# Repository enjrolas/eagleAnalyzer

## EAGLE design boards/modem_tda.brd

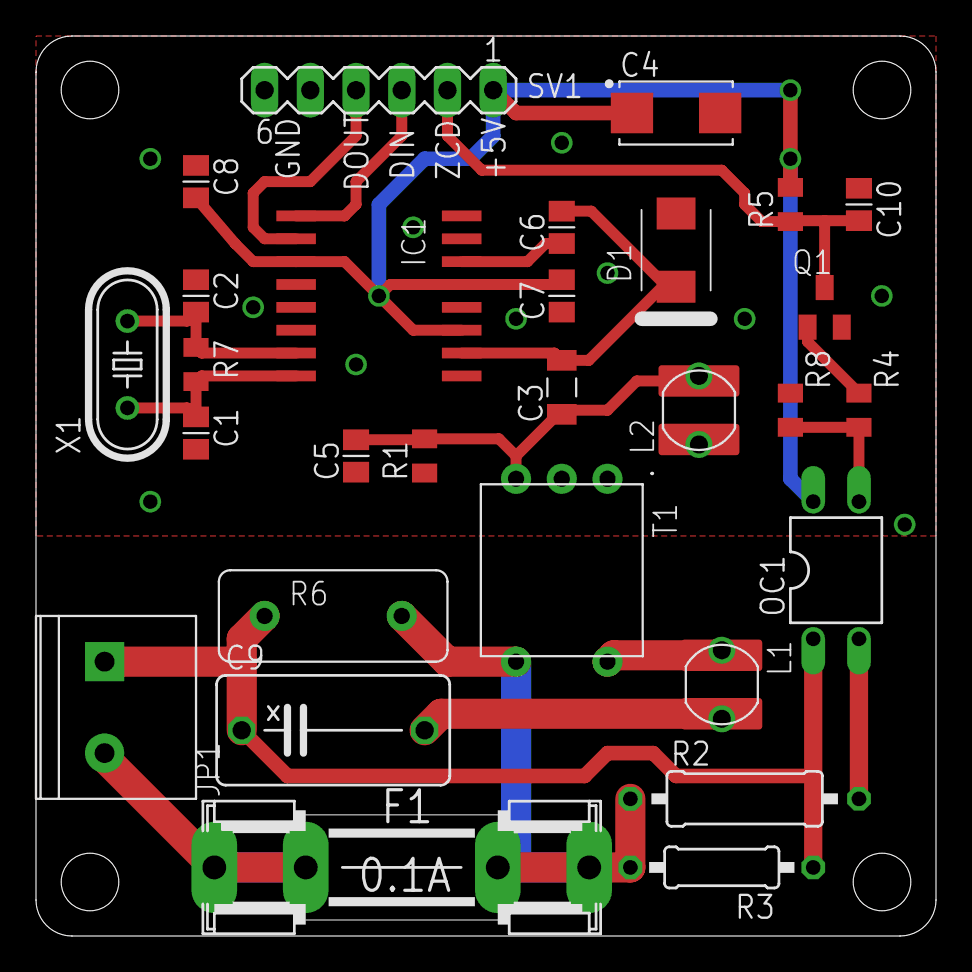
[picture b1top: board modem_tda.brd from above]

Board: 2 copper layers, 50.0 x 50.0 mm, 29 parts (0 on the bottom side), 18 nets.

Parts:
C1, C2: 27pF; CAPC2012X145AN
C3: 10 uF 16V; CAPC3215X168N
C4: 100 uF; CAPMP6032X150N
C5, C6, C7, C8: 0.1uF; CAPC2012X145AN
C9: 47nF; XC10B6
C10: 2.2nF; CAPC2012X145AN
D1: SMBJ7.0A; SMBJ
F1: 0.1A; SHK20L
IC1: TDA5051; SO16W
JP1: BLUE_TERM
L1: 47 uH; CD43
L2: 22 uH; CD43
OC1: PC814; DIL04
Q1: 2N3904SOT23; SOT23-BEC
R1: 100; RESC2012X70N
R2: 220K; 0309/12
R3: 1M; 0207/10
R4: 1K; RESC2012X70N
R5: 10K; RESC2012X70N
R6: 10D391K; MOV-10D
R7: 2.2M; RESC2012X70N
R8: 4.7K; RESC2012X70N
SV1: MA06-1
T1: MU-78250; 6-PIN-DIL
X1: 8MHz; HC49/S

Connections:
+5V: C4.+, C7.2, C8.2, IC1.3, IC1.11, IC1.13, OC1.4, R5.2, SV1.1
GND: C1.2, C2.2, C4.-, C5.1, C7.1, C8.1, C10.1, D1.A, IC1.5, IC1.9, IC1.12, L2.1, Q1.E, R1.1, R8.1, SV1.5, SV1.6, T1.1
unnamed: F1.1A, F1.1B, JP1.2
unnamed: F1.2A, F1.2B, R2.1, R3.2, R6.2, T1.4
unnamed: C9.1, JP1.1, OC1.1, R3.1, R6.1
unnamed: OC1.2, R2.2
unnamed: C9.2, L1.2
unnamed: L1.1, T1.6
unnamed: OC1.3, R4.1, R8.2
unnamed: C3.1, C5.2, L2.2, R1.2, T1.3
unnamed: C3.2, C6.2, D1.C, IC1.10
unnamed: C10.2, Q1.C, R5.1, SV1.2
unnamed: C6.1, IC1.14
unnamed: C2.1, IC1.7, R7.2, X1.2
unnamed: C1.1, IC1.8, R7.1, X1.1
unnamed: IC1.1, SV1.3
unnamed: IC1.2, SV1.4
unnamed: Q1.B, R4.2

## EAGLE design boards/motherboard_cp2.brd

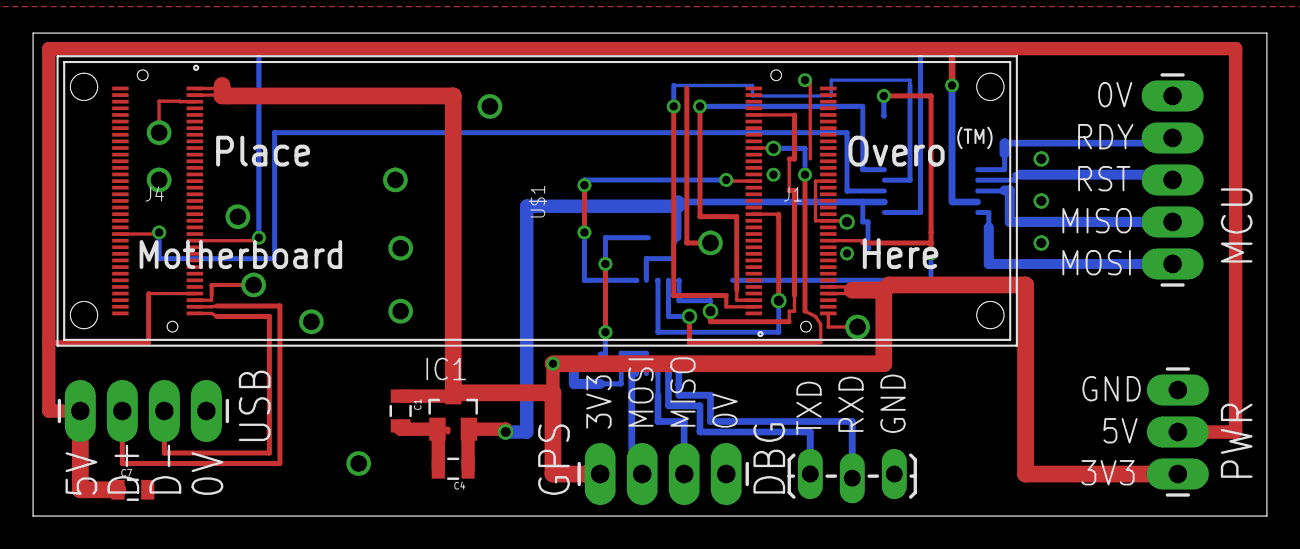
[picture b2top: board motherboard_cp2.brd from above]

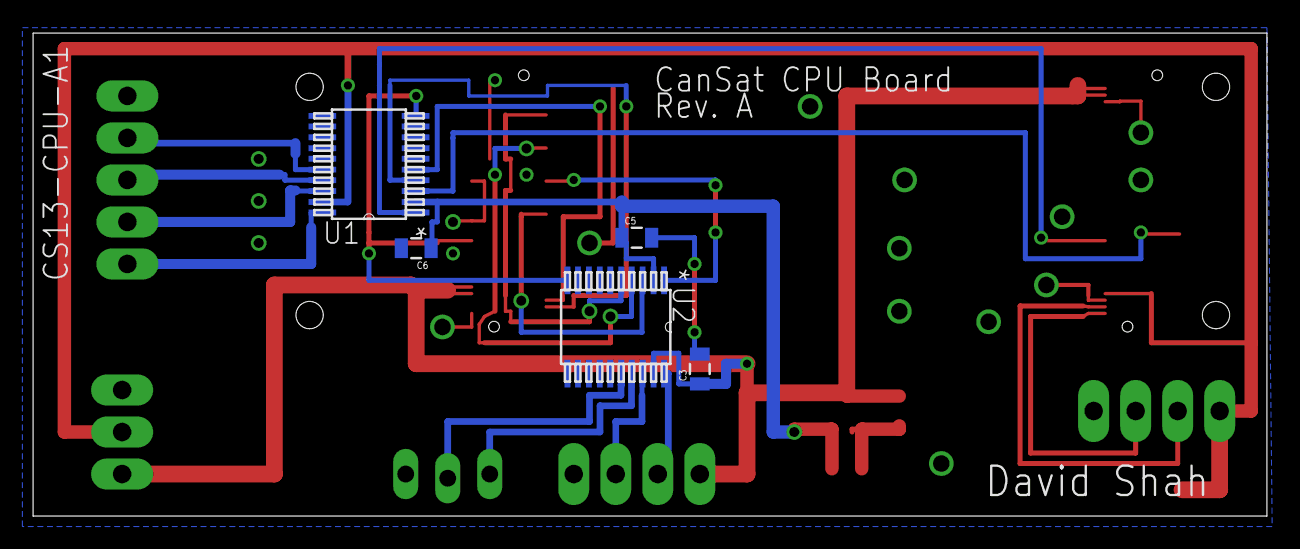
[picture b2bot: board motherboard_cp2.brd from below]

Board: 2 copper layers, 74.6 x 29.2 mm, 15 parts (5 on the bottom side), 23 nets.

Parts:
C1, C3, C4, C5, C6, C7: 1uF; 0805
DEBUG: 1X03_LOCK_LONGPADS
GPS: 1X04_LONGPADS
IC1: MCP1703CB; SOT23
MCU: 1X05_LONGPADS
PWR: 1X03_LONGPADS
U1, U2: TXS0108E_PW_20; PW20
U$1: OVERO
USB: 1X04_LONGPADS

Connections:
1.8V: C4.1, C5.1, C6.1, IC1.2, U1.2, U2.2
3.3V: C1.1, C3.1, GPS.1, IC1.3, PWR.1, U2.19, U$1.J1_66, U$1.J1_67, U$1.J4_1, U$1.J4_2
5V: C7.1, PWR.2, U1.19, U$1.J4_32, USB.1
DBG_RXD: DEBUG.2, U2.16
DBG_TXD: DEBUG.1, U2.17
GND: C1.2, C3.2, C4.2, C5.2, C6.2, C7.2, DEBUG.3, GPS.4, IC1.1, MCU.5, PWR.3, U1.11, U1.12, U1.13, U1.14, U1.15, U2.11, U2.12, U2.13, U2.14, U2.15, U$1.J1_50, U$1.J1_56, U$1.J1_70, U$1.J4_3, U$1.J4_33, USB.4
GPS_RXD: GPS.3, U2.18
GPS_TXD: GPS.2, U2.20
MCU_RDY: MCU.4, U1.16
MCU_RST: MCU.3, U1.17
MCU_RXD: MCU.2, U1.18
MCU_TXD: MCU.1, U1.20
RDY: U1.5, U$1.J1_3
SYSEN: U1.10, U2.10, U$1.J1_59
UART1_RTS: U1.4, U$1.J1_2
UART1_RXD: U1.3, U$1.J4_48
UART1_TXD: U1.1, U$1.J4_24
UART2_RXD: U2.3, U$1.J1_16
UART2_TXD: U2.1, U$1.J1_21
UART3_RXD: U2.5, U$1.J1_31
UART3_TXD: U2.4, U$1.J1_26
USB_DM: U$1.J4_35, USB.3
USB_DP: U$1.J4_34, USB.2

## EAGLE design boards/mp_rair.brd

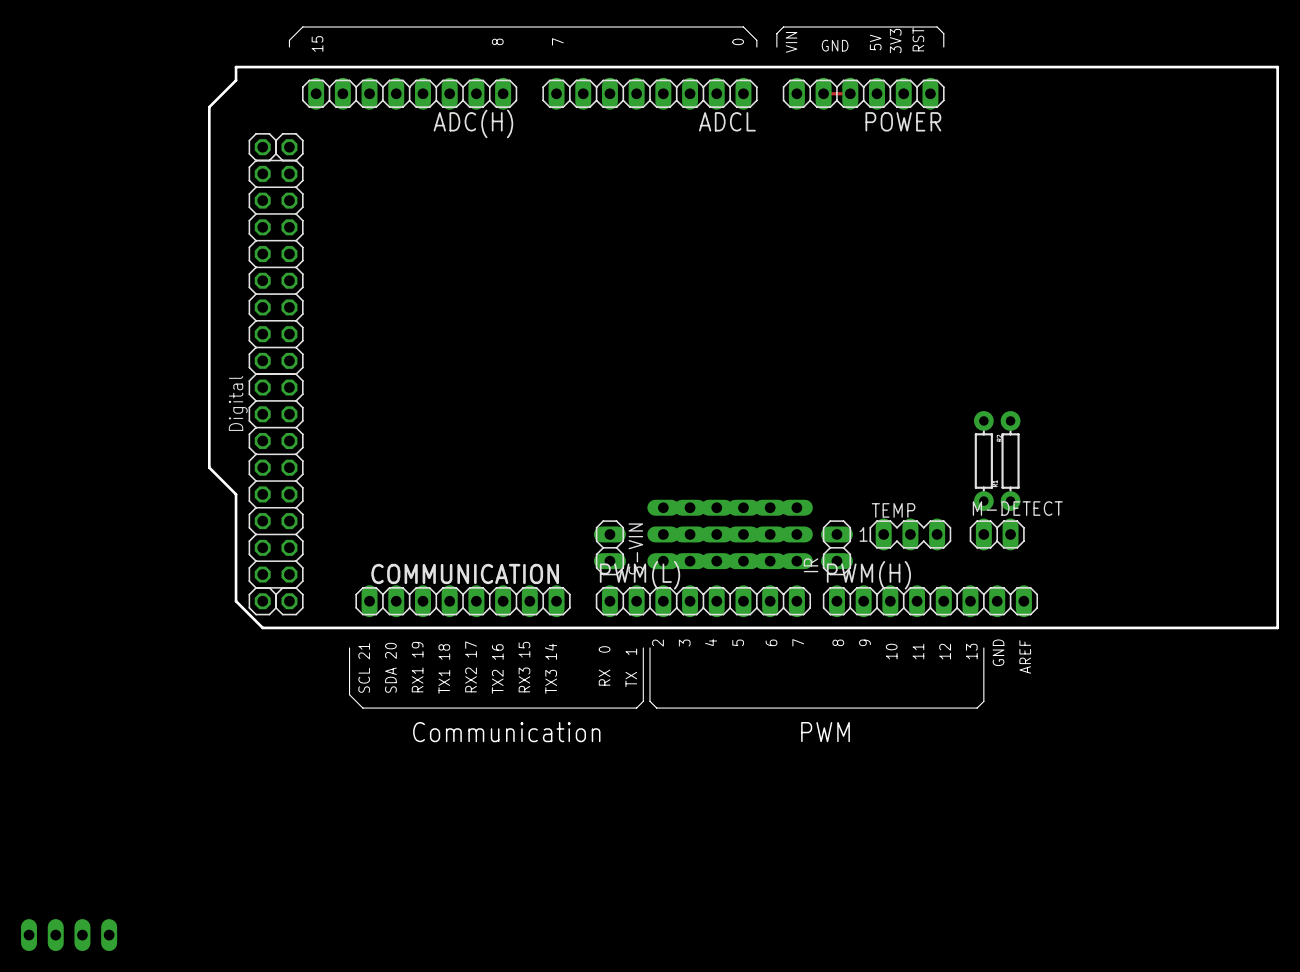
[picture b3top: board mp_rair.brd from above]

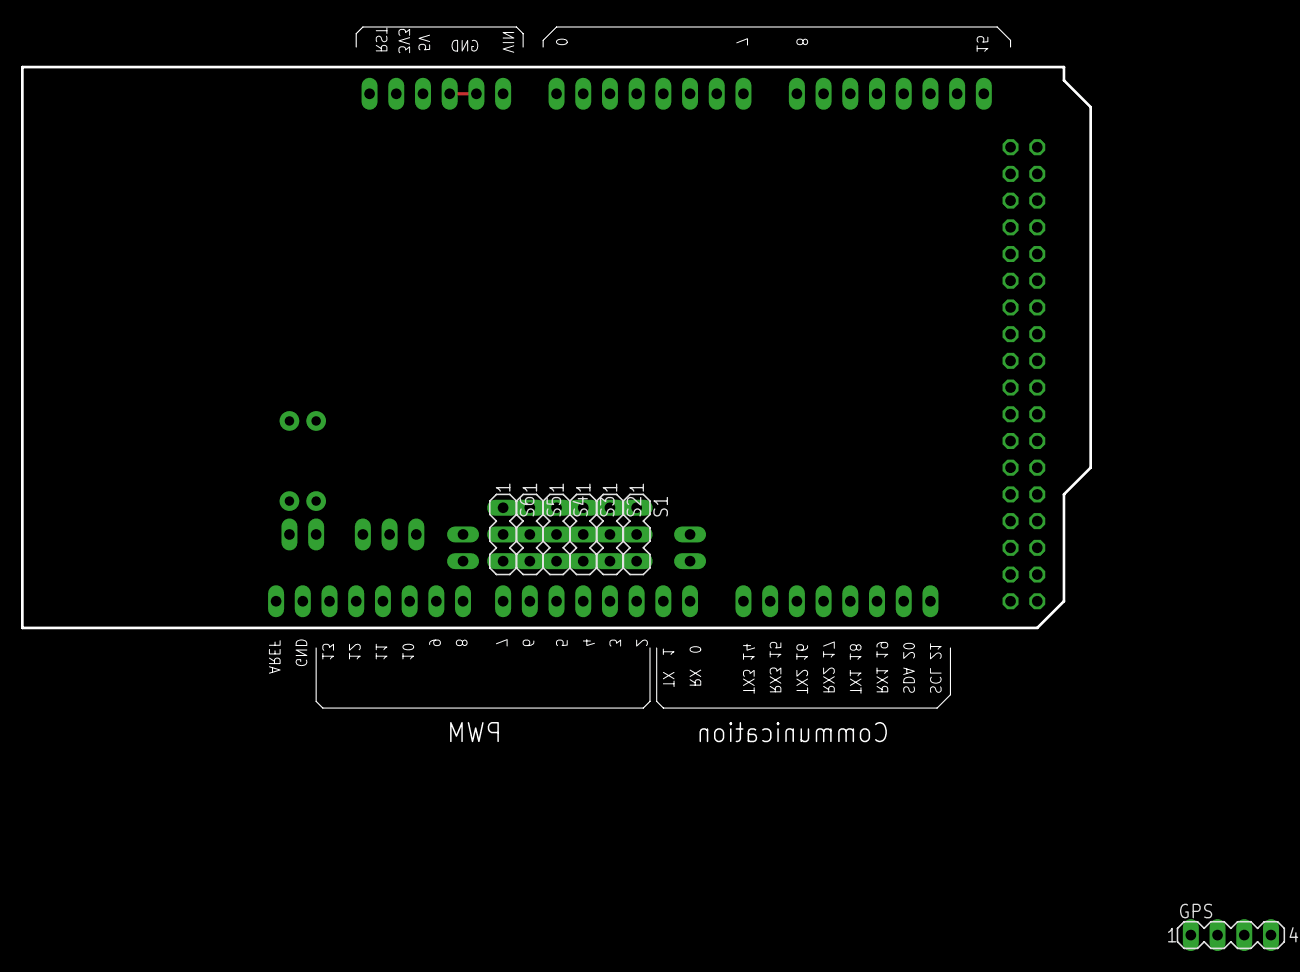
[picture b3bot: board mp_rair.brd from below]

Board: 2 copper layers, 101.6 x 53.3 mm, 25 parts (7 on the bottom side), 13 nets.

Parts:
ADC(H): 1X08
ADCL: 1X08
COMMUNICATION: 1X08
GPS: MA04-1
IR: 1X02
JP1, JP2: Digital; 2X08
JP3, JP4, JP5, JP6: 1X01
M-DETECT: 1X02
POWER: 1X06
PWM(H): 1X08
PWM(L): 1X08
R1, R2: AXIAL-0.3
S1, S2, S3, S4, S5, S6: MA03-1
S-VIN: 1X02
TEMP: MA03-1

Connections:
+5V: JP3.1, JP4.1, POWER.3, TEMP.1
ADC0: ADCL.1, R1.P$2, R2.P$1
ADC1: ADCL.2, TEMP.2
GND: IR.2, JP5.1, JP6.1, M-DETECT.2, POWER.4, POWER.5, PWM(H).7, R1.P$1, TEMP.3
unnamed: S1.3, S2.3, S3.3, S4.3, S5.3, S6.3, S-VIN.2
unnamed: S1.2, S2.2, S3.2, S4.2, S5.2, S6.2, S-VIN.1
unnamed: M-DETECT.1, R2.P$2
PWM02: PWM(L).3, S1.1
PWM03: PWM(L).4, S2.1
PWM05: PWM(L).6, S4.1
PWM06: PWM(L).7, S5.1
PWM07: PWM(L).8, S6.1
PWM08: IR.1, PWM(H).1

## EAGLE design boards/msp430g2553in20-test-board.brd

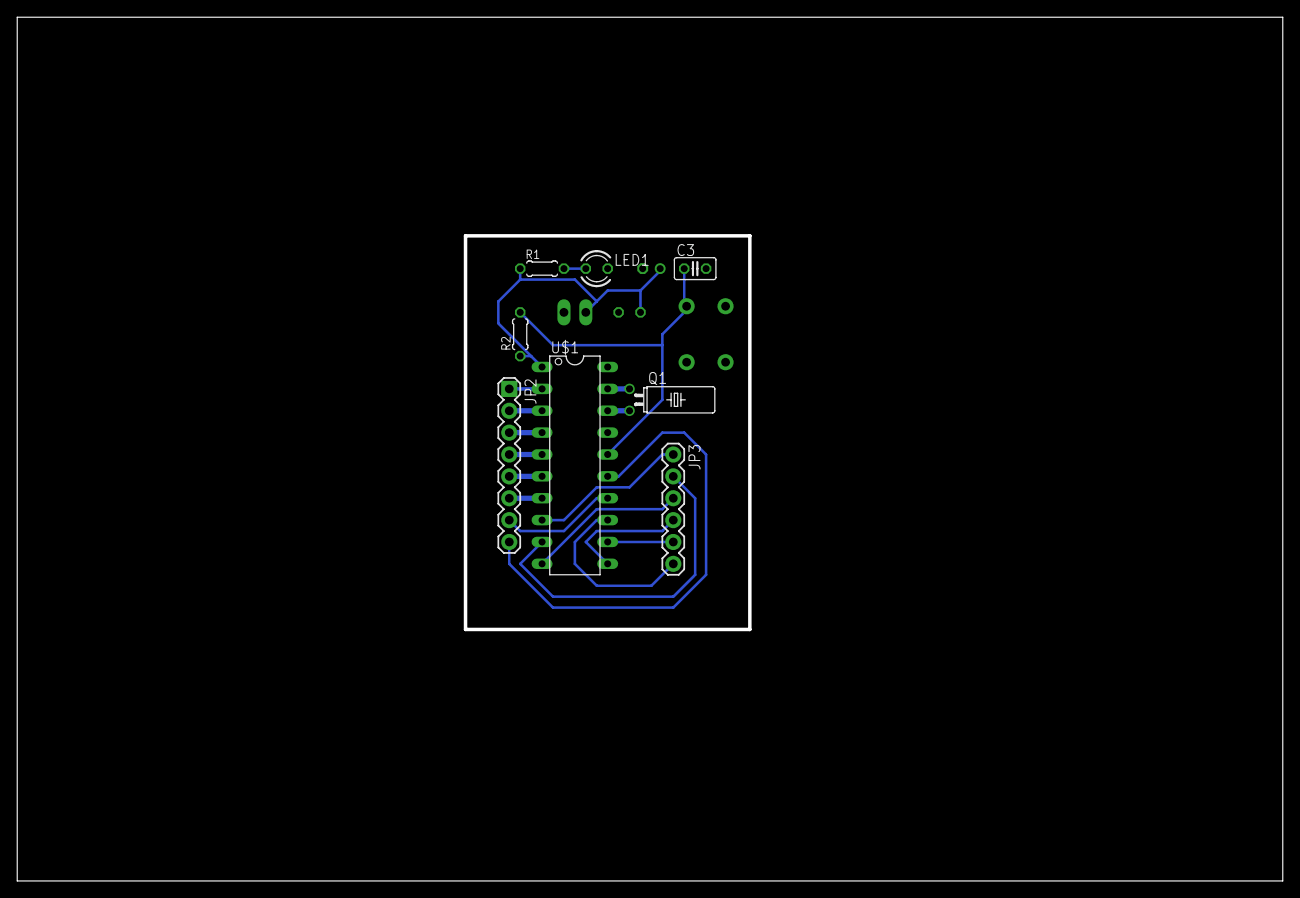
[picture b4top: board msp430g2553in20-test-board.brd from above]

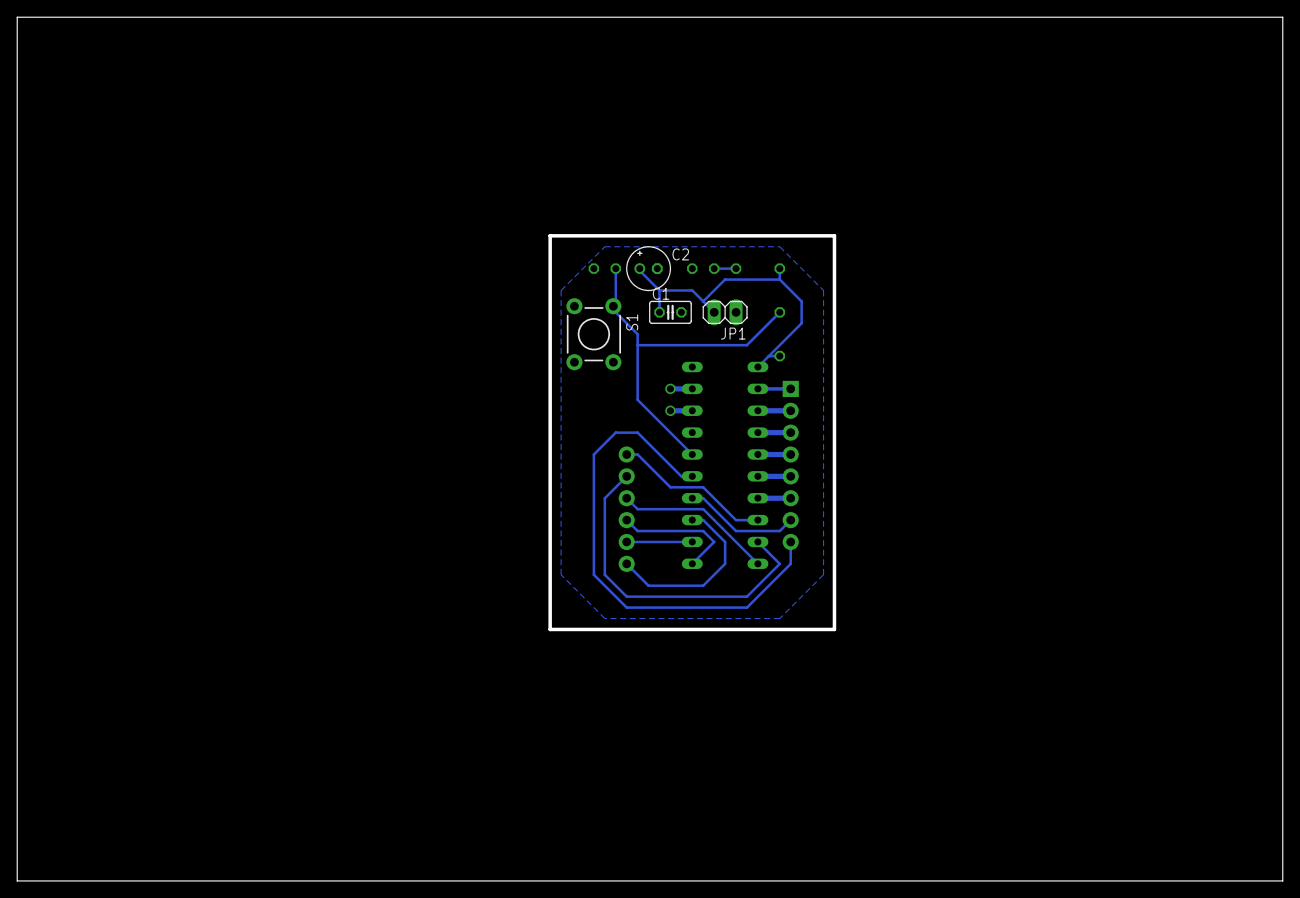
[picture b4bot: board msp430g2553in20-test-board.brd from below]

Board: 2 copper layers, 147.0 x 100.3 mm, 12 parts (4 on the bottom side), 20 nets.

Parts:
C1: 100nF; C025-025X050
C2: 10uF/25V; E2-5
C3: 1nF; C025-025X050
JP1: PWR; 1X02
JP2: PORT1; 1X08
JP3: PORT2; 1X06
LED1: GREEN; LED3MM
Q1: 32768; TC38H
R1: 270; 0204/5
R2: 47K; 0204/5
S1: SWITCH-MOMENTARY-2PTH; TACTILE-PTH
U$1: G2XX3---N20; N20

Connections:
GND: C1.2, C2.-, C3.2, JP1.1, LED1.K, S1.3, U$1.20
unnamed: JP2.1, U$1.2
unnamed: Q1.1, U$1.19
unnamed: Q1.2, U$1.18
unnamed: LED1.A, R1.2
unnamed: JP2.2, U$1.3
unnamed: JP2.3, U$1.4
unnamed: JP2.4, U$1.5
unnamed: JP2.5, U$1.6
unnamed: JP2.6, U$1.7
unnamed: JP2.7, U$1.14
unnamed: JP2.8, U$1.15
unnamed: JP3.1, U$1.8
unnamed: JP3.4, U$1.11
unnamed: JP3.5, U$1.12
unnamed: JP3.6, U$1.13
unnamed: JP3.2, U$1.9
unnamed: JP3.3, U$1.10
RST: C3.1, R2.2, S1.1, U$1.16
VCC: C1.1, C2.+, JP1.2, R1.1, R2.1, U$1.1

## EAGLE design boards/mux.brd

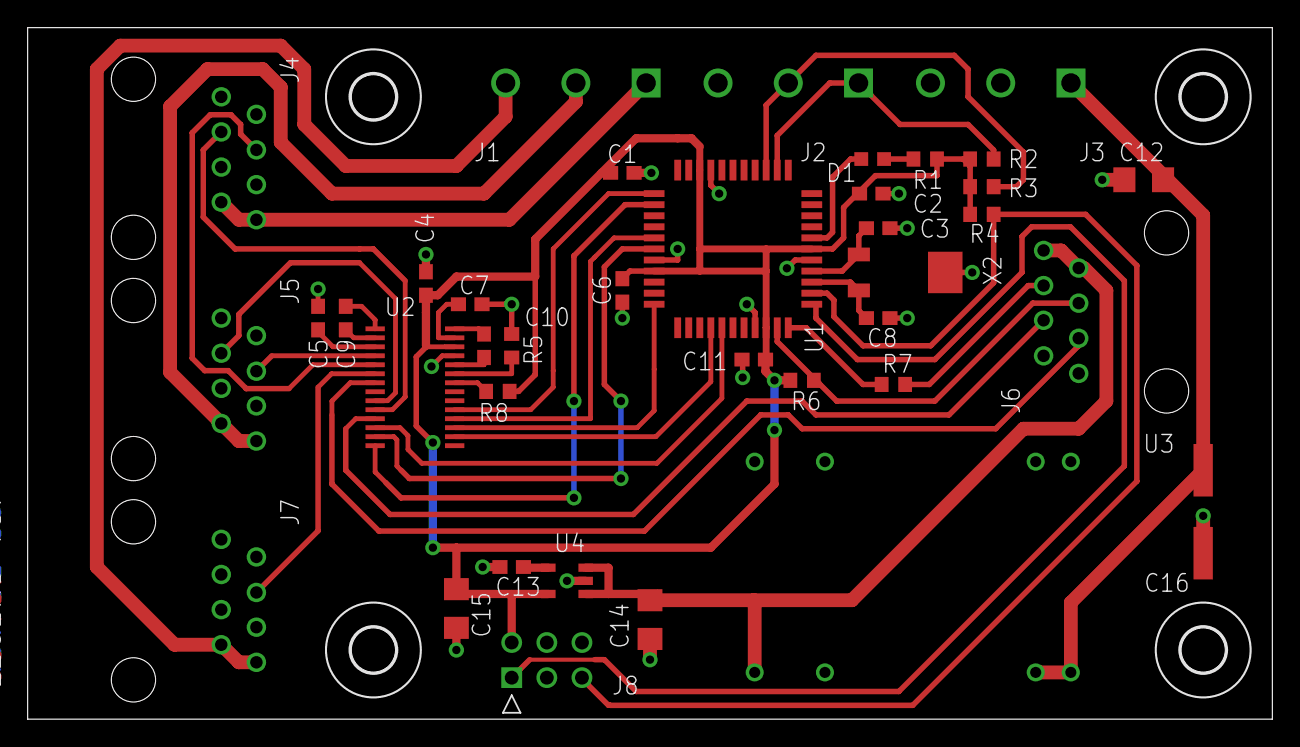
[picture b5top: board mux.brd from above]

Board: 2 copper layers, 90.0 x 50.0 mm, 42 parts (0 on the bottom side), 41 nets.

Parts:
C1, C2, C4, C5, C6, C7, C9, C10, C11: 220n; C0603
C3, C8: 10p; C0603
C12, C14, C15: 4u7; C1206
C13: 10n; C0603
C16: 100u; PANASONIC_E
D1: SML-D12U8W; LED_0603
H1, H2, H3, H4: MOUNT-HOLE3.2; 3,2
J1, J2, J3: MKDSN1.5/3-5.08; MKDSN_1.5_3_5.08
J4, J5, J6, J7: MOLEX95501-2881; RJ45
J8: HEADER_3x2; HEADER-3X2-0.1
R1: 330R; R0603
R2, R3, R6: 4k7; R0603
R4, R5, R8: 10k; R0603
R7: 22R; R0603
U1: ATxmega32A4; TQFP44
U2: MAX3241ECUI+; TSSOP28
U3: TEL5-1211; TEL5
U4: LP2985-33; SOT23-5
X2: MS1V-T1K

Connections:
12V: C12.1, C16.+, J3.1, U3.22, U3.23
12V1: J1.2, J5.7, J5.8
12V2: J1.1, J4.7, J4.8
12V3: J1.3, J7.7, J7.8
+3V3: C1.1, C2.1, C4.1, C6.1, C11.1, C15.1, J8.2, R1.2, R2.1, R3.1, R4.1, R6.1, R8.1, U1.9, U1.19, U1.31, U1.39, U2.26, U4.5
+5V: C14.1, J6.7, J6.8, U3.14, U4.1, U4.3
GND: C1.2, C2.2, C3.2, C4.2, C5.2, C6.2, C7.2, C8.2, C11.2, C12.2, C13.2, C14.2, C15.2, C16.-, J2.3, J3.2, J3.3, J4.1, J4.2, J5.1, J5.2, J6.1, J6.2, J7.1, J7.2, J8.6, R5.1, U1.8, U1.18, U1.30, U1.38, U2.25, U3.2, U3.3, U3.16, U4.2, X2.3
MODE1: J2.1, R2.2, U1.2
MODE2: J2.2, R3.2, U1.3
unnamed: C7.1, U2.27
unnamed: C5.1, U2.3
unnamed: C13.1, U4.4
unnamed: C3.1, U1.37, X2.1
unnamed: C8.1, U1.36, X2.2
unnamed: C10.2, U2.28
unnamed: C10.1, U2.24
unnamed: C9.2, U2.1
unnamed: C9.1, U2.2
unnamed: R8.2, U2.22
unnamed: J8.1, U1.34
unnamed: J8.5, R4.2, U1.35
unnamed: R5.2, U2.23
unnamed: R7.1, U1.33
unnamed: D1.2, R1.1
unnamed: D1.1, U1.40
RX1: U1.12, U2.19
RX2: U1.16, U2.18
RX3: U1.22, U2.17
RXD: U1.26, U2.16
RXIN1: J5.4, U2.4
RXIN2: J4.4, U2.5
RXIN3: J7.4, U2.6
RXIND: J6.3, U2.7
RXIND_TTL: J6.5, R6.2, U1.32
TX1: U1.13, U2.14
TX2: U1.17, U2.13
TXD: U1.27, U2.12
TXOUT1: J5.3, U2.9
TXOUT2: J4.3, U2.10
TXOUTD: J6.4, U2.11
TXOUTD_TTL: J6.6, R7.2

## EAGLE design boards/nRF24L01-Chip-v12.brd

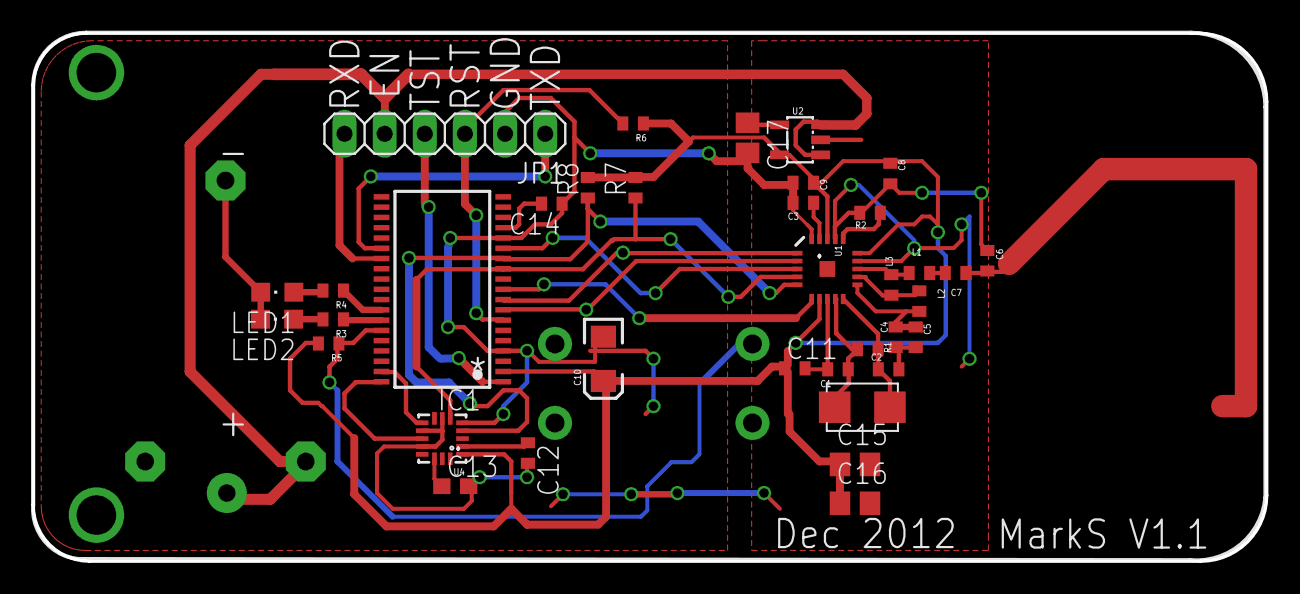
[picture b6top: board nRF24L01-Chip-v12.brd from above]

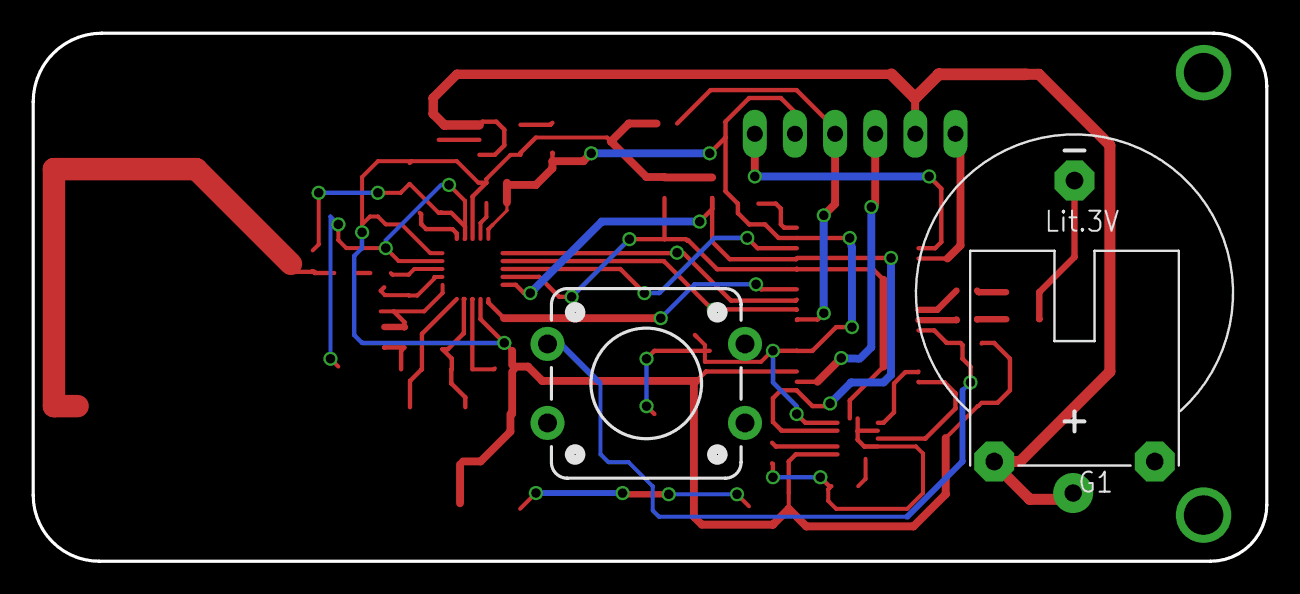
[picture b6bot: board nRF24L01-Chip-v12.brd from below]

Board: 2 copper layers, 78.1 x 33.4 mm, 38 parts (2 on the bottom side), 33 nets.

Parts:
C1, C2: 22pF; C0402
C3: 33nF; C0402
C4: 2.2nF; C0402
C5: 4.7pF; C0402
C6: 1.0pF; C0402
C7: 1.5pF; C0402
C8, C14: 10nF; C0402
C9: 1nF; C0402
C10: 10uF; EIA3216
C11, C12: 0.1u; C0402
C13: 4.7u; C0603
C15, C16: 10nF; C0805
C17: 0.01uF; C0805
G1: CR2032H
IC1: MSP430F2274IDA; TSSOP38_R-PDSO-G38-DA
JP1: 1X06
L1: 3.9nH; C0402
L2: 2.7nH; C0402
L3: 8.2nH; C0402
LED1, LED2: CHIPLED_0805
Q1: SMAQ-5032A; CRSYTAL1
R1: 1M; C0402
R2: 22K; C0402
R3, R4: 400R; C0402
R5, R6: 47k; C0402
R7, R8: 4.7k; R0402
S2: SWITCH-MOMENTARY-212MM; TACTILE-PTH-12MM
U1: NRF24L01SMD; QFN20
U2: 3.3V; SOT23-5
U4: MMA8452Q; QFN-16_0.5MM

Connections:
ANT: C6.2, C7.2
GND: C1.2, C2.2, C3.2, C4.2, C5.2, C6.1, C8.1, C9.1, C10.C, C11.2, C12.2, C13.2, C14.1, C15.2, C16.2, C17.2, G1.-, IC1.4, IC1.15, JP1.2, LED1.C, LED2.C, R2.2, S2.3, U1.0, U1.8, U1.14, U1.17, U1.20, U2.2, U4.5, U4.7, U4.10, U4.12
unnamed: C1.1, Q1.P$3, R1.1, U1.9
unnamed: IC1.1, JP1.4
unnamed: L2.2, L3.1, U1.12
unnamed: R2.1, U1.16
unnamed: C3.1, U1.19
unnamed: L1.1, L3.2, U1.13
unnamed: C4.1, C5.1, L2.1, U1.11
unnamed: IC1.9, U1.1
unnamed: C7.1, L1.2
unnamed: IC1.8, U1.2
unnamed: IC1.14, U1.3
unnamed: IC1.12, R7.1, U1.4, U4.6
unnamed: IC1.13, R8.1, U1.5, U4.4
unnamed: IC1.25, JP1.1
unnamed: IC1.10, U1.6
unnamed: IC1.32, R3.1
unnamed: LED2.A, R3.2
unnamed: LED1.A, R4.2
unnamed: IC1.33, R5.1, S2.1
unnamed: C17.1, U2.4
unnamed: IC1.26, JP1.6
unnamed: C14.2, IC1.16
unnamed: IC1.31, R4.1
unnamed: C2.1, Q1.P$4, R1.2, U1.10
unnamed: IC1.7, JP1.3, R6.2
unnamed: C12.1, U4.2
unnamed: IC1.38, U4.11
unnamed: IC1.37, U4.9
unnamed: C13.1, U4.14
RAW: G1.+, JP1.5, U2.1, U2.3
VCC: C8.2, C9.2, C10.A, C11.1, C15.1, C16.1, IC1.2, R5.2, R6.1, R7.2, R8.2, U1.7, U1.15, U1.18, U2.5, U4.1

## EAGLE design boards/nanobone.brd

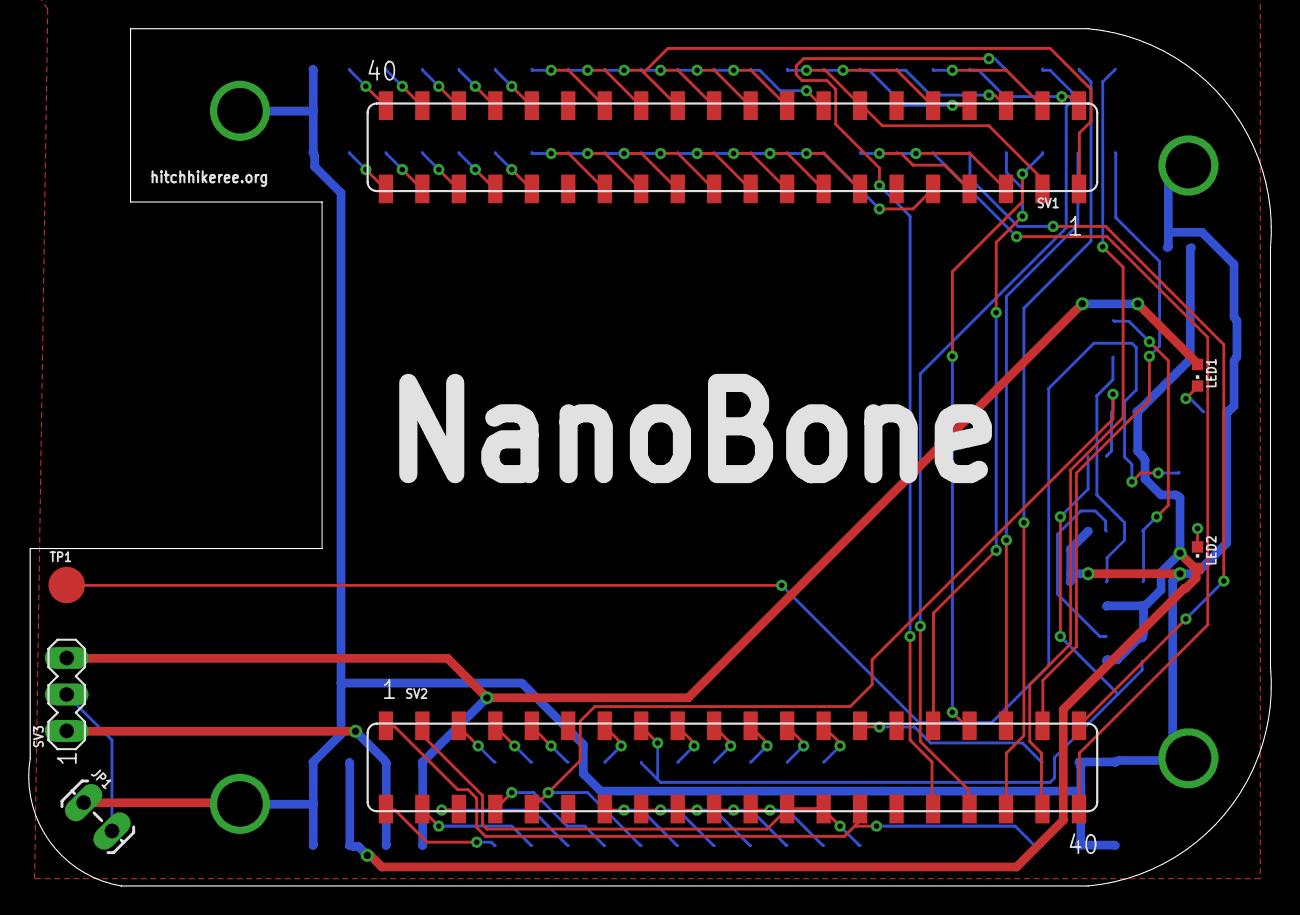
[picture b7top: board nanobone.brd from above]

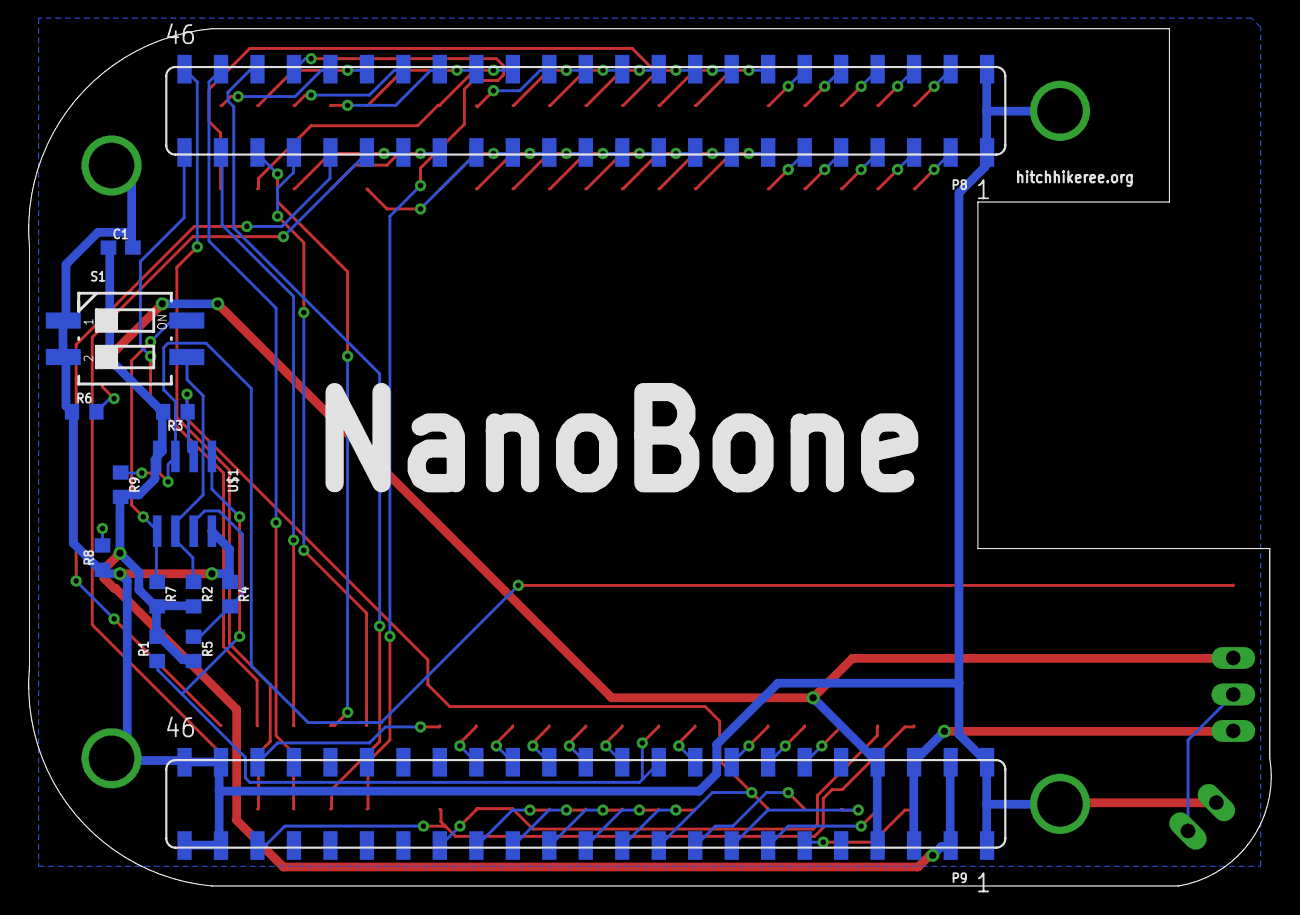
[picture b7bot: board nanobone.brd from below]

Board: 2 copper layers, 86.5 x 59.7 mm, 25 parts (14 on the bottom side), 78 nets.

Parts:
C1: 0.1u; C0603
H1, H2, H3, H4: HOLE
JP1: 1X02_LOCK_LONGPADS
LED1: blue; CHIPLED_0603
LED2: green; CHIPLED_0603
P8, P9: FE23-2_SMD
R1, R3: 5.6K, 5%; R0603
R2, R5, R7: 4.75K; R0603
R4: 4.75K, DNI; R0603
R6: 150; R0603
R8: 50; R0603
R9: 10K; R0603
S1: 219-02; CTS-219-02
SV1, SV2: FE20-2
SV3: MA03-1
TP1: TPB2,54; B2,54
U$1: SOIC8

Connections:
+3V3: C1.1, LED2.A, P9.3, P9.4, R1.2, R2.2, R3.2, R5.2, R7.2, R9.2, U$1.8
+5V: LED1.A, P9.7, P9.8, SV3.3
CLKOUT2: P9.41, SV2.1, SV2.28
EHRPWM1A: P9.14, SV2.7
EHRPWM1B: P9.16, SV2.9
EHRPWM2A: P8.19, SV1.21
EHRPWM2B: P8.13, SV1.27
GND: C1.2, H1.GND, H2.GND, H3.GND, H4.GND, JP1.1, P8.1, P8.2, P9.1, P9.2, P9.43, P9.44, P9.45, P9.46, R4.1, R6.1, R8.1, S1.1, S1.2, U$1.4
GPIO0_7: P9.42, SV2.27
GPIO0_26: P8.14, SV1.28
GPIO0_27: P8.17, SV1.23
GPIO1_0: P8.25, SV1.15
GPIO1_1: P8.24, SV1.18
GPIO1_2: P8.5, SV1.37
GPIO1_3: P8.6, SV1.38
GPIO1_4: P8.23, SV1.17
GPIO1_5: P8.22, SV1.20
GPIO1_6: P8.3, SV1.39
GPIO1_7: P8.4, SV1.40
GPIO1_12: P8.12, SV1.32
GPIO1_13: P8.11, SV1.31
GPIO1_14: P8.16, SV1.26
GPIO1_15: P8.15, SV1.25
GPIO1_16: P9.15, SV2.6
GPIO1_17: P9.23, SV2.16
GPIO1_28: P9.12, SV2.5
GPIO1_29: P8.26, SV1.16
GPIO1_30: P8.21, SV1.19
GPIO1_31: P8.20, SV1.22
GPIO2_1: P8.18, SV1.1, SV1.24
GPIO2_6: P8.45, SV2.37
GPIO2_7: P8.46, SV2.38
GPIO2_8: P8.43, SV2.35
GPIO2_9: P8.44, SV2.36
GPIO2_10: P8.41, SV2.33
GPIO2_11: P8.42, SV2.34
GPIO2_12: P8.39, SV2.31
GPIO2_13: P8.40, SV2.32
GPIO2_22: P8.27, SV1.13
GPIO2_23: P8.29, SV1.9
GPIO2_24: P8.28, SV1.3, SV1.14
GPIO2_25: P8.30, SV1.10
GPIO3_19: P9.27, SV2.20
GPIO3_21: P9.25, SV2.18
I2C1_SCL: P9.17, SV2.8
I2C1_SDA: P9.18, SV2.13
I2C2_SCL: P9.19, R3.1, SV2.10, U$1.6
I2C2_SDA: P9.20, R1.1, SV2.15, U$1.5
unnamed: R7.1, S1.4, U$1.1
unnamed: R2.1, S1.3, U$1.2
unnamed: R4.2, R5.1, U$1.3
unnamed: JP1.2, SV3.2
unnamed: R9.1, TP1.TP, U$1.7
unnamed: LED1.C, R6.2
unnamed: LED2.C, R8.2
SPI1_CS0: P9.28, SV2.23
SPI1_D0: P9.29, SV2.22
SPI1_D1: P9.30, SV2.25
SPI1_SCLK: P9.31, SV2.3, SV2.24, SV2.26
TIMER4: P8.7, SV1.35
TIMER5: P8.9, SV1.33
TIMER6: P8.10, SV1.34
TIMER7: P8.8, SV1.36
UART1_RXD: P9.26, SV2.21
UART1_TXD: P9.24, SV2.19
UART2_RXD: P9.22, SV2.17
UART2_TXD: P9.21, SV2.14
UART3_CTSN: P8.36, SV1.4
UART3_RTSN: P8.34, SV1.6
UART4_CTSN: P8.35, SV2.40
UART4_RTSN: P8.33, SV1.5
UART4_RXD: P9.11, SV2.2
UART4_TXD: P9.13, SV2.4
UART5_CTSN: P8.31, SV1.7
UART5_RTSN: P8.32, SV1.8
UART5_RXD: P8.38, SV1.2
UART5_TXD: P8.37, SV2.39
VDD: P9.5, P9.6, SV3.1

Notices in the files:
parts and their libraries:
SparkFun-Connectors: Licensing: CC v3.0 Share-Alike You are welcome to use this library for commercial purposes.
